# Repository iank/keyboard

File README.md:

Custom keyboard. Derived from the [pierce keyboard](https://github.com/durken1/pierce)

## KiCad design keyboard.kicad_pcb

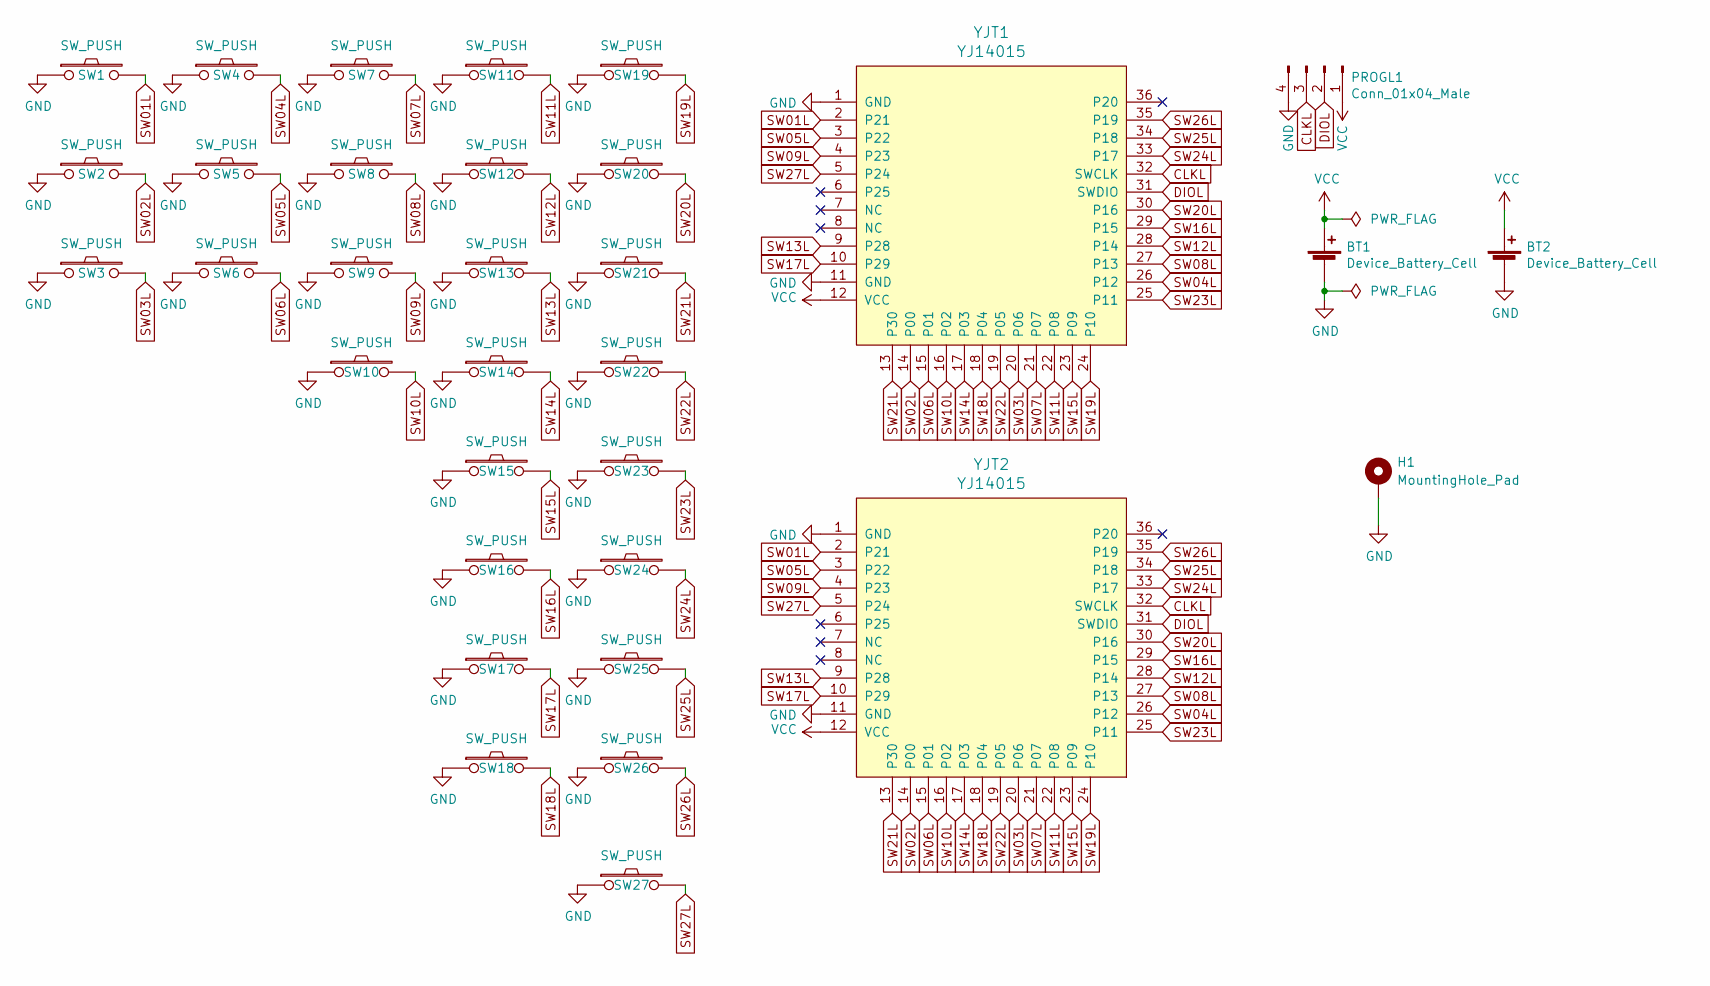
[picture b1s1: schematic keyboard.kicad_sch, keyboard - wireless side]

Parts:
BT1, BT2: Device_Battery_Cell; BatteryHolder_Keystone_3034_1x20mm
H1: MountingHole_Pad; Tenting_Puck
PROGL1: Conn_01x04_Male; PinHeader_1x04_P2.54mm_Horizontal
SW1, SW2, SW3, SW4, SW5, SW6, SW7, SW8, SW9, SW10, SW11, SW12, SW13, SW14, SW15, SW16, SW17, SW18, SW19, SW20, SW21, SW22, SW23, SW24, SW25, SW26, SW27: SW_PUSH; MX_ALPS_PG1350_noLed
YJT1, YJT2: YJ14015; YJ-14015

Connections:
CLKL: PROGL1.3, YJT1.32 (SWCLK), YJT2.32 (SWCLK)
DIOL: PROGL1.2, YJT1.31 (SWDIO), YJT2.31 (SWDIO)
GND: BT1.2 (-), BT2.2 (-), H1.1, PROGL1.4, SW1.1, SW2.1, SW3.1, SW4.1, SW5.1, SW6.1, SW7.1, SW8.1, SW9.1, SW10.1, SW11.1, SW12.1, SW13.1, SW14.1, SW15.1, SW16.1, SW17.1, SW18.1, SW19.1, SW20.1, SW21.1, SW22.1, SW23.1, SW24.1, SW25.1, SW26.1, SW27.1, YJT1.1 (GND), YJT1.11 (GND), YJT2.1 (GND), YJT2.11 (GND)
SW01L: SW1.2, YJT1.2 (P21), YJT2.2 (P21)
SW02L: SW2.2, YJT1.14 (P00), YJT2.14 (P00)
SW03L: SW3.2, YJT1.20 (P06), YJT2.20 (P06)
SW04L: SW4.2, YJT1.26 (P12), YJT2.26 (P12)
SW05L: SW5.2, YJT1.3 (P22), YJT2.3 (P22)
SW06L: SW6.2, YJT1.15 (P01), YJT2.15 (P01)
SW07L: SW7.2, YJT1.21 (P07), YJT2.21 (P07)
SW08L: SW8.2, YJT1.27 (P13), YJT2.27 (P13)
SW09L: SW9.2, YJT1.4 (P23), YJT2.4 (P23)
SW10L: SW10.2, YJT1.16 (P02), YJT2.16 (P02)
SW11L: SW11.2, YJT1.22 (P08), YJT2.22 (P08)
SW12L: SW12.2, YJT1.28 (P14), YJT2.28 (P14)
SW13L: SW13.2, YJT1.9 (P28), YJT2.9 (P28)
SW14L: SW14.2, YJT1.17 (P03), YJT2.17 (P03)
SW15L: SW15.2, YJT1.23 (P09), YJT2.23 (P09)
SW16L: SW16.2, YJT1.29 (P15), YJT2.29 (P15)
SW17L: SW17.2, YJT1.10 (P29), YJT2.10 (P29)
SW18L: SW18.2, YJT1.18 (P04), YJT2.18 (P04)
SW19L: SW19.2, YJT1.24 (P10), YJT2.24 (P10)
SW20L: SW20.2, YJT1.30 (P16), YJT2.30 (P16)
SW21L: SW21.2, YJT1.13 (P30), YJT2.13 (P30)
SW22L: SW22.2, YJT1.19 (P05), YJT2.19 (P05)
SW23L: SW23.2, YJT1.25 (P11), YJT2.25 (P11)
SW24L: SW24.2, YJT1.33 (P17), YJT2.33 (P17)
SW25L: SW25.2, YJT1.34 (P18), YJT2.34 (P18)
SW26L: SW26.2, YJT1.35 (P19), YJT2.35 (P19)
SW27L: SW27.2, YJT1.5 (P24), YJT2.5 (P24)
VCC: BT1.1 (+), BT2.1 (+), PROGL1.1, YJT1.12 (VCC), YJT2.12 (VCC)

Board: 4 copper layers, 37 parts (2 on the bottom side), 31 nets, no tracks yet.

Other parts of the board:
Ref**: Val**; M2_HOLE_v2
Ref**#2, Ref**#3, Ref**#4: Val**; M2_HOLE_v2

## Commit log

2023-07-22 Import from pierce; add some keys; move to kicad 7
2023-07-23 kibot
2023-07-23 kibot ERC/schematic/BOM
2023-07-23 Update PCB
2023-07-23 Approximate layout
2023-09-12 Adjust spacing and stagger, add splitkb tenting puck
2023-09-12 Add board outline
2023-09-12 set trace / spacing, 4 layers
2023-09-12 fix spacing, add a mod key
